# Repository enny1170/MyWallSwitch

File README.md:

# MyWallSwitch
MySensors based Wall Switch EU

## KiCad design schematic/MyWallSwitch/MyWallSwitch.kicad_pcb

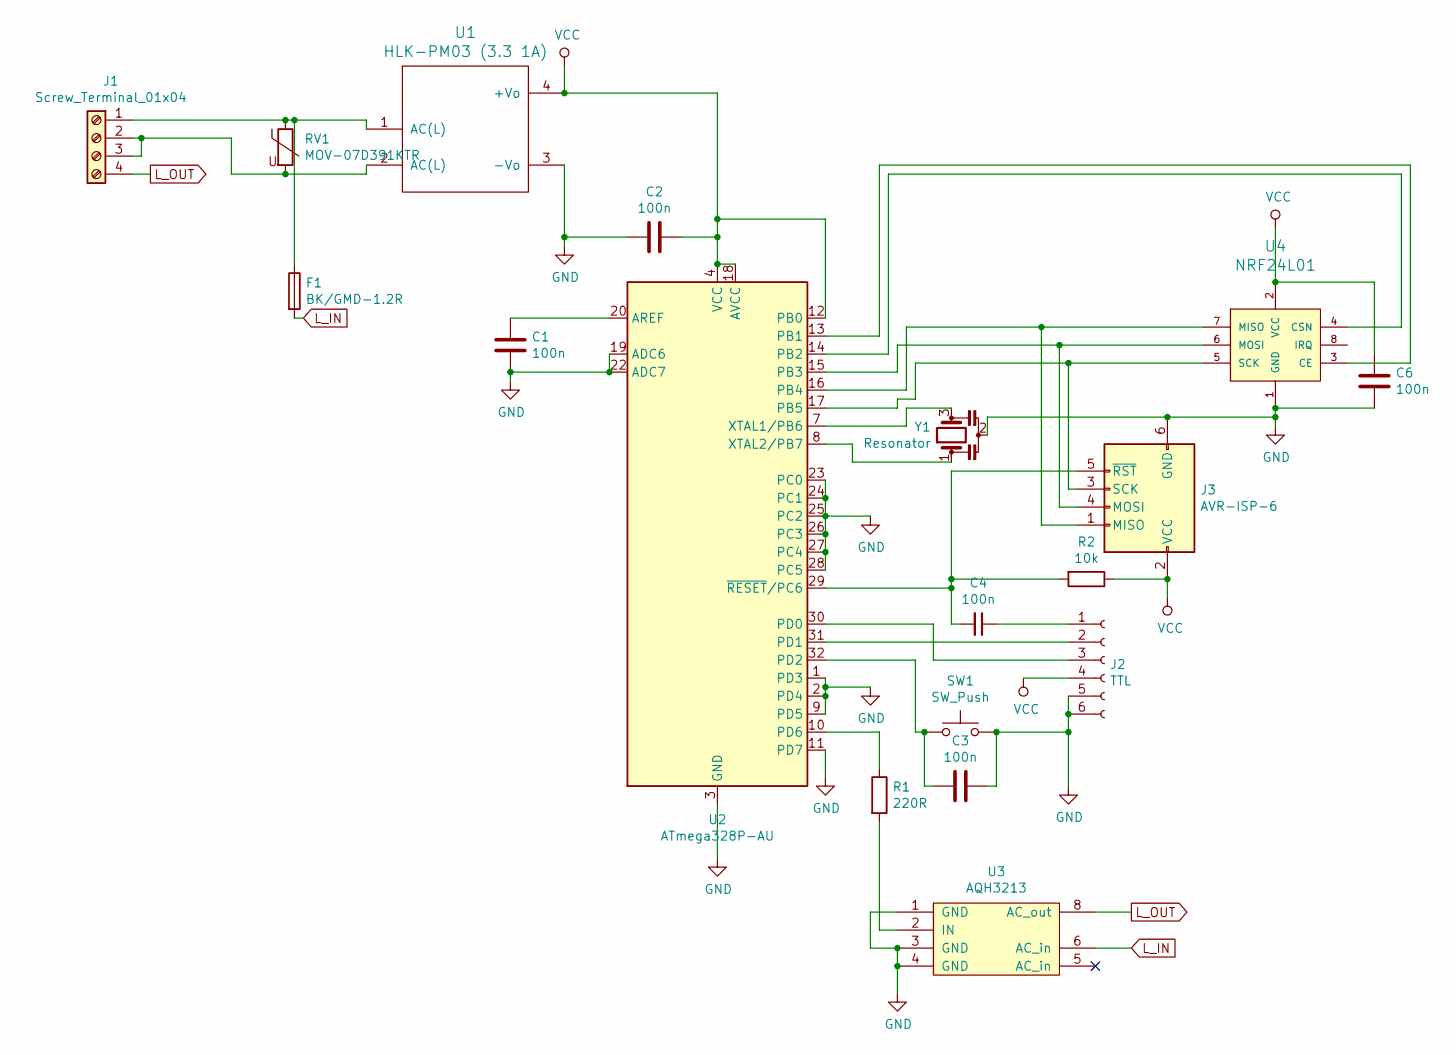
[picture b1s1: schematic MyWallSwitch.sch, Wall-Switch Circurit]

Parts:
C1, C2, C3, C4, C6: 100n; C_0603_HandSoldering
F1: BK/GMD-1.2R; Fuseholder5x20_horiz_open_universal_Type-III
J1: Screw_Terminal_01x04; TerminalBlock_bornier-4_P5.08mm
J2: TTL; Pin_Header_Straight_1x06_Pitch2.54mm
J3: AVR-ISP-6; Pin_Header_Straight_2x03_Pitch2.54mm_SMD
R1: 220R; R_0603_HandSoldering
R2: 10k; R_0603_HandSoldering
RV1: MOV-07D391KTR; RV_Disc_D7_W5.5_P5
SW1: SW_Push; SW_SPST_EVQPE1
U1: HLK-PM03 (3.3 1A); HLK-PM01
U2: ATmega328P-AU; TQFP-32_7x7mm_Pitch0.8mm
U3: AQH3213; DIP-8_W7.62mm_SMDSocket_SmallPads
U4: NRF24L01; NRF24L01-SMD
Y1: Resonator; Resonator_Ceramic

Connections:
GND: C1.2, C2.2, C3.1, C6.2, J2.5, J2.6, J3.6 (GND), SW1.2, U1.3 (-Vo), U2.1 (PD3), U2.2 (PD4), U2.3 (GND), U2.5 (GND), U2.9 (PD5), U2.11 (PD7), U2.19 (ADC6), U2.21 (GND), U2.22 (ADC7), U2.23 (PC0), U2.24 (PC1), U2.25 (PC2), U2.26 (PC3), U2.27 (PC4), U2.28 (PC5), U3.1 (GND), U3.3 (GND), U3.4 (GND), U4.1 (GND), Y1.2
L_IN: F1.2, U3.6 (AC_in)
L_OUT: J1.4, U3.8 (AC_out)
unnamed: C1.1, U2.20 (AREF)
unnamed: C3.2, SW1.1, U2.32 (PD2)
unnamed: C4.1, J2.1
unnamed: C4.2, J3.5 (~RST), R2.2, U2.29 (~RESET~/PC6)
unnamed: F1.1, J1.1, RV1.1, U1.1 (AC(L))
unnamed: J1.2, J1.3, RV1.2, U1.2 (AC(L))
unnamed: J2.2, U2.31 (PD1)
unnamed: J2.3, U2.30 (PD0)
unnamed: J3.1 (MISO), U2.16 (PB4), U4.7 (MISO)
unnamed: J3.3 (SCK), U2.17 (PB5), U4.5 (SCK)
unnamed: J3.4 (MOSI), U2.15 (PB3), U4.6 (MOSI)
unnamed: R1.1, U2.10 (PD6)
unnamed: R1.2, U3.2 (IN)
unnamed: U2.7 (XTAL1/PB6), Y1.3
unnamed: U2.8 (XTAL2/PB7), Y1.1
unnamed: U2.13 (PB1), U4.3 (CE)
unnamed: U2.14 (PB2), U4.4 (CSN)
VCC: C2.1, C6.1, J2.4, J3.2 (VCC), R2.1, U1.4 (+Vo), U2.4 (VCC), U2.6 (VCC), U2.12 (PB0), U2.18 (AVCC), U4.2 (VCC)

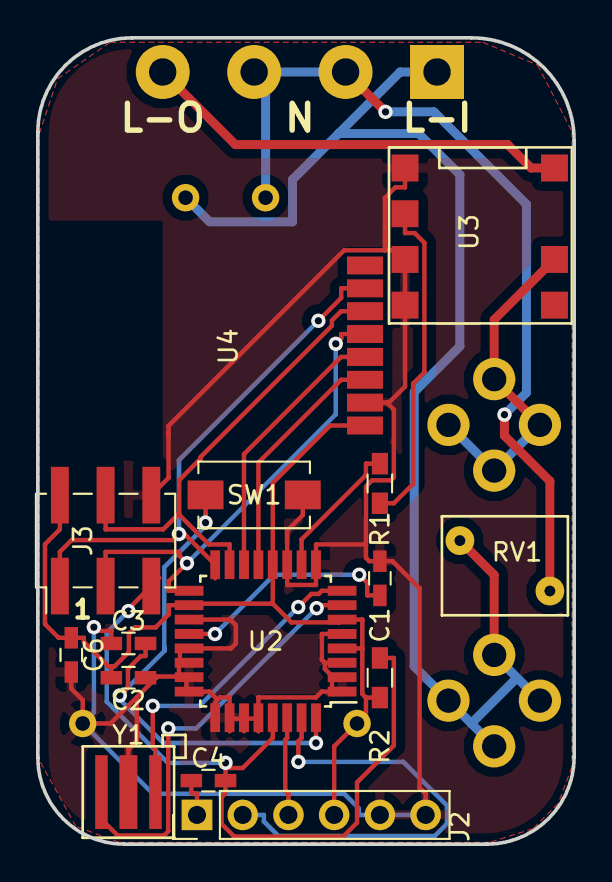
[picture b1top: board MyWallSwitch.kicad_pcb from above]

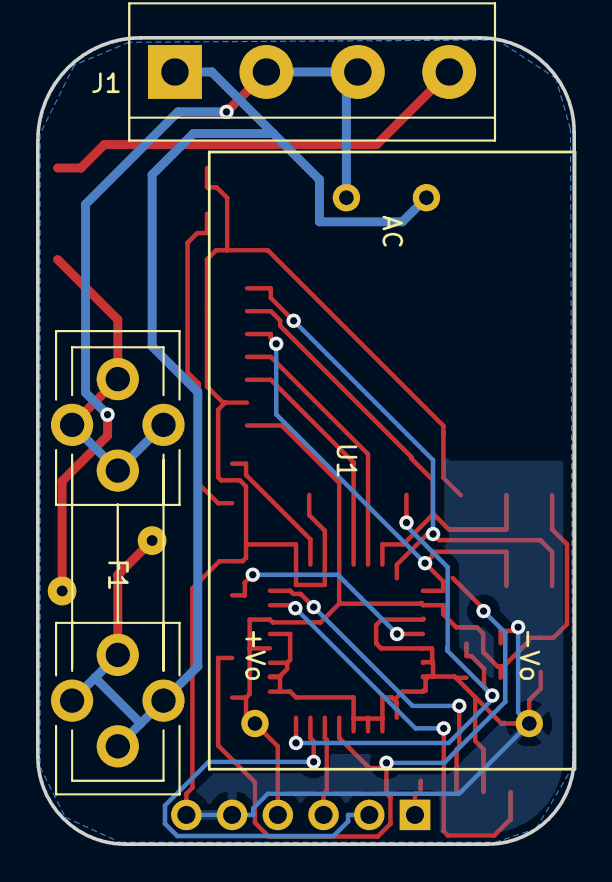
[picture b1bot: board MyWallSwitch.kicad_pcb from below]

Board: 2 copper layers, 29.8 x 44.8 mm, 18 parts (3 on the bottom side), 21 nets.

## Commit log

2019-01-02 working Version
2019-01-03 schematic added
2019-01-17 cleanup
2019-04-23 firmware build
2019-04-29 Fix Shematic and PCB
2019-05-03 Sensor signal removed, repeater added V1.1
2019-05-03 finished
2019-05-04 added Firmware Descriptions
2019-05-04 Firmware pdf
2019-05-06 enclosure objects added
